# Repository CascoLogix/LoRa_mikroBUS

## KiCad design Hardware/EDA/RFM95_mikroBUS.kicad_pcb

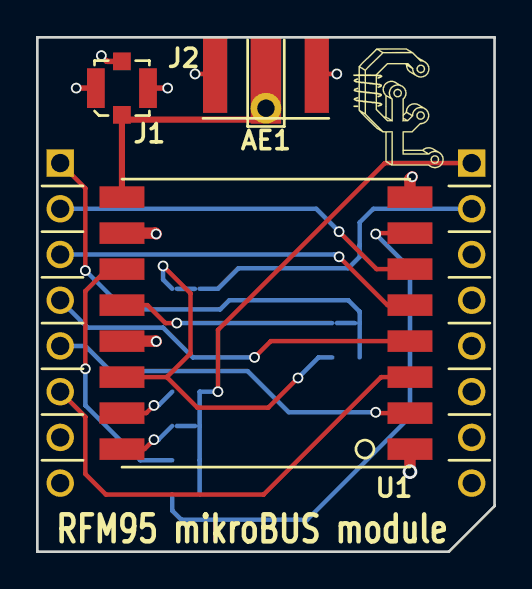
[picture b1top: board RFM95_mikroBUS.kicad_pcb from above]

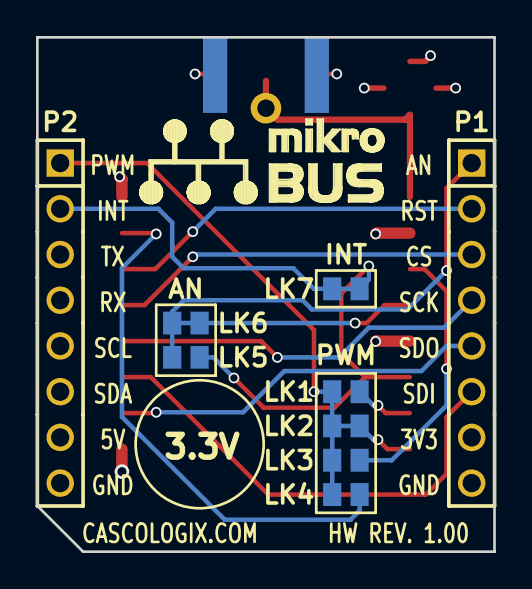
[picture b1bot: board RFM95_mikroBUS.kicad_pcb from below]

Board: 4 copper layers, 25.4 x 28.6 mm, 14 parts (9 on the bottom side), 17 nets.

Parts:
AE1: Antenna_Helical_RA; ANTENNA_HELICAL_RA
G1: Casco_Logix_Logo; Casco_Logix_Logo_6x6MM
J1: u.FL; U.FL-R-SMT
J2: SMA; SMA_EDGE
LK1, LK3, LK4, LK5: NO; SOLDER_LINK_NO
LK2, LK6, LK7: NC; SOLDER_LINK_NC
P1, P2: HEADER_M_2.54MM_1R8P_ST_AU_PTH
U1: RFM95W

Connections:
+3.3V: P1.7, U1.13
AN: LK5.1, LK6.1, P1.1
CS: P1.3, U1.5
DIO0: LK5.2, LK7.2, U1.14
DIO1: LK1.2, U1.15
DIO2: LK2.2, U1.16
DIO3: LK3.2, U1.11
DIO4: LK6.2, U1.12
DIO5: LK4.2, U1.7
GND: J1.2, J1.3, J1.4, J2.2, J2.3, P1.8, P2.8, U1.1, U1.8, U1.10
INT: LK7.1, P2.2
MISO: P1.5, U1.2
MOSI: P1.6, U1.3
unnamed: AE1.1, J1.1, J2.1, U1.9
PWM: LK1.1, LK2.1, LK3.1, LK4.1, P2.1
RST: P1.2, U1.6
SCK: P1.4, U1.4

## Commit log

2015-12-03 Added EDA files.
2015-12-03 Moved EDA files into proper directory.
2015-12-03 Added gerbers, schematic drawing, and updated KiCAD project files.
2015-12-23 Added ground connections to SMA edge connector. Removed extra *.pro file in parent directory.
2016-01-03 Changed name from LoRa mikroBUS to RFM95 mikroBUS. Added zero ohm resistor and solder links for RF path and DIO configuration options.
2016-01-07 Peer-review package
2016-01-09 Added several files. Final release and boards ordered from OSHPark.
2016-01-23 Corrected SMA Edge connector footprint and regenerated gerber files.
2017-12-12 Updated PCB renderings to include images of three different variants (Helical, SMA and uFL antenna).
2017-12-12 Updated logo on schematic and regenerated pdf.
2017-12-25 Added and updated images. Added pinout diagram. Updated logo on schematic.
2018-04-07 Added logo to silkscreen and standardized ref des sizes.
2018-04-07 Cleaning up branch for removal.
